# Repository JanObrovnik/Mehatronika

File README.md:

V tem repozitoriju so navedeni primeri kod v povezavi z našim izdelkom razvojne ploščice ESP32­-C3.

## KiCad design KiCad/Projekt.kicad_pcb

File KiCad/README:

Tukaj je celoten izdelek (vezje in ploščica) v KiCad-u..

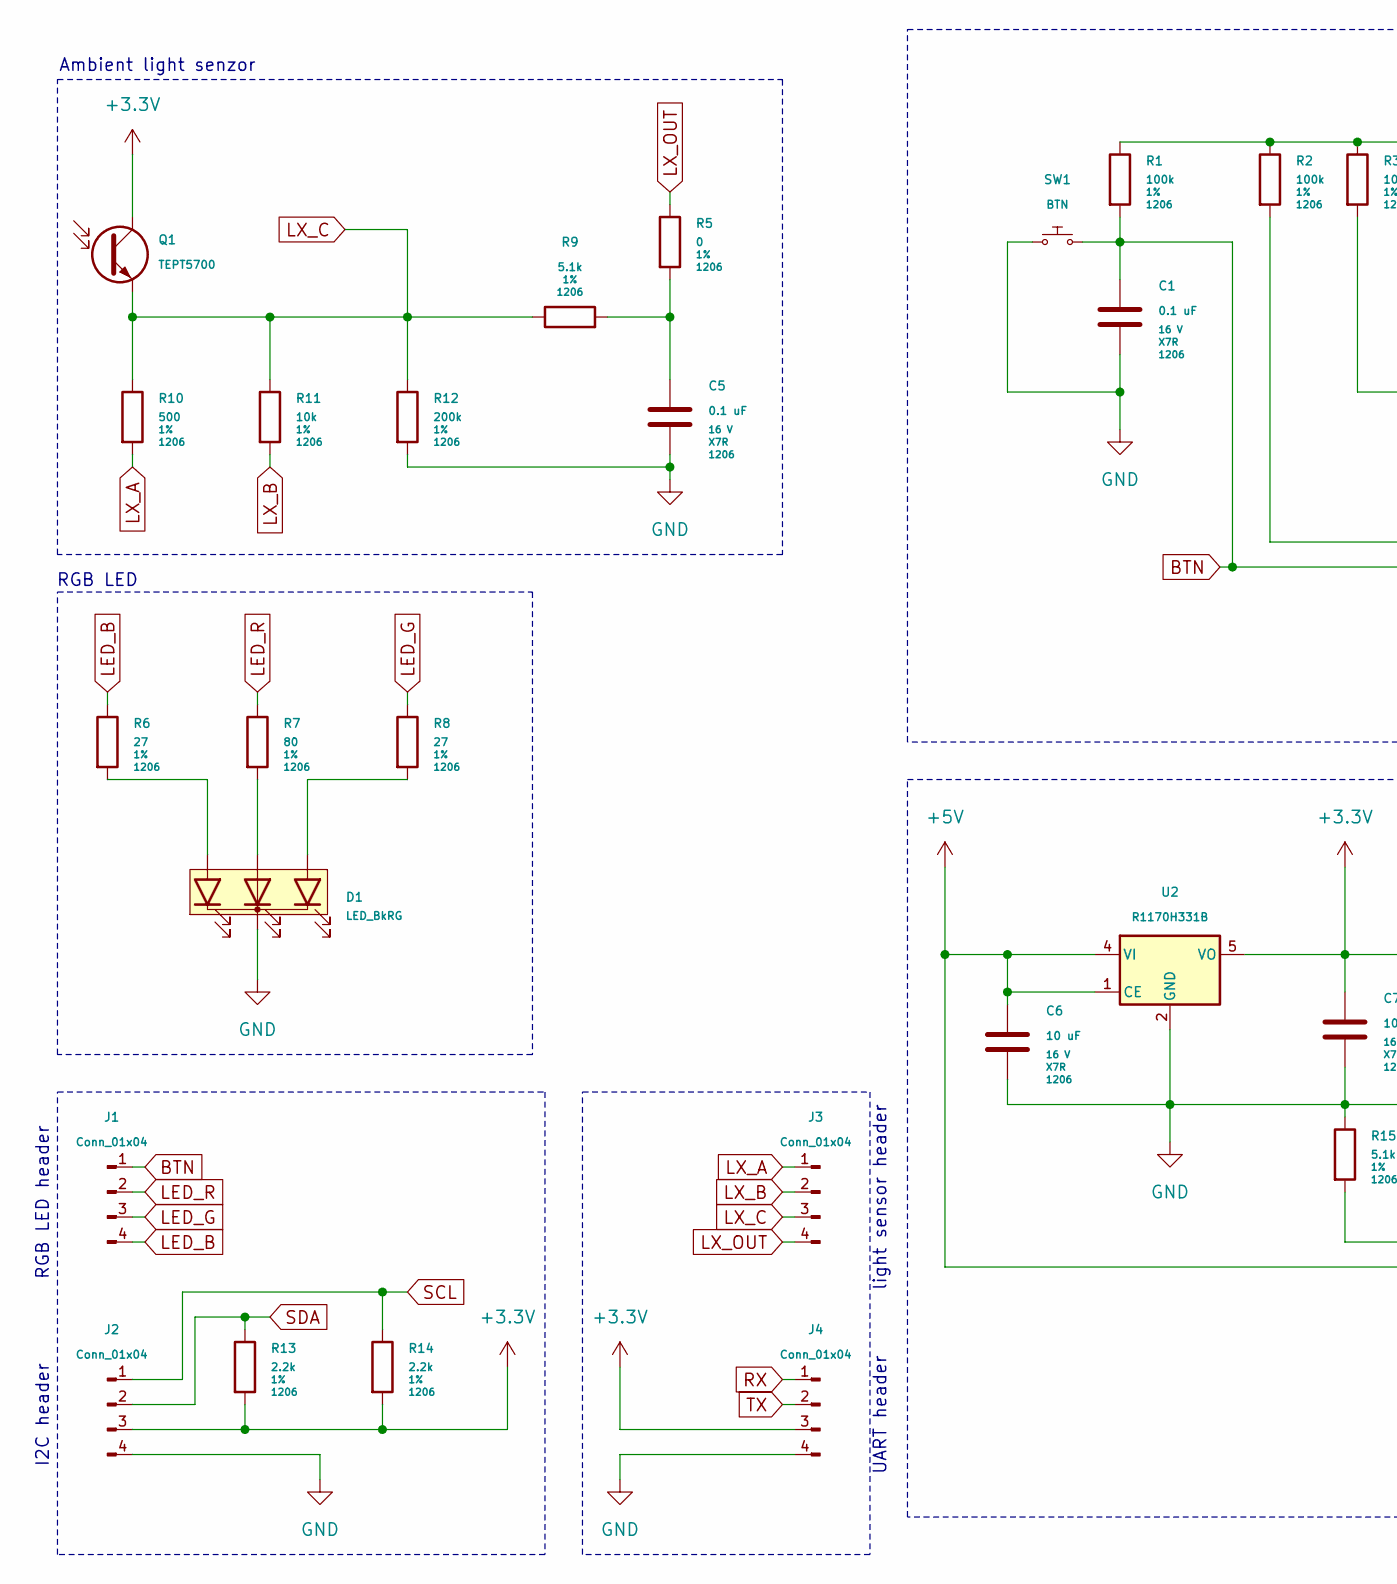
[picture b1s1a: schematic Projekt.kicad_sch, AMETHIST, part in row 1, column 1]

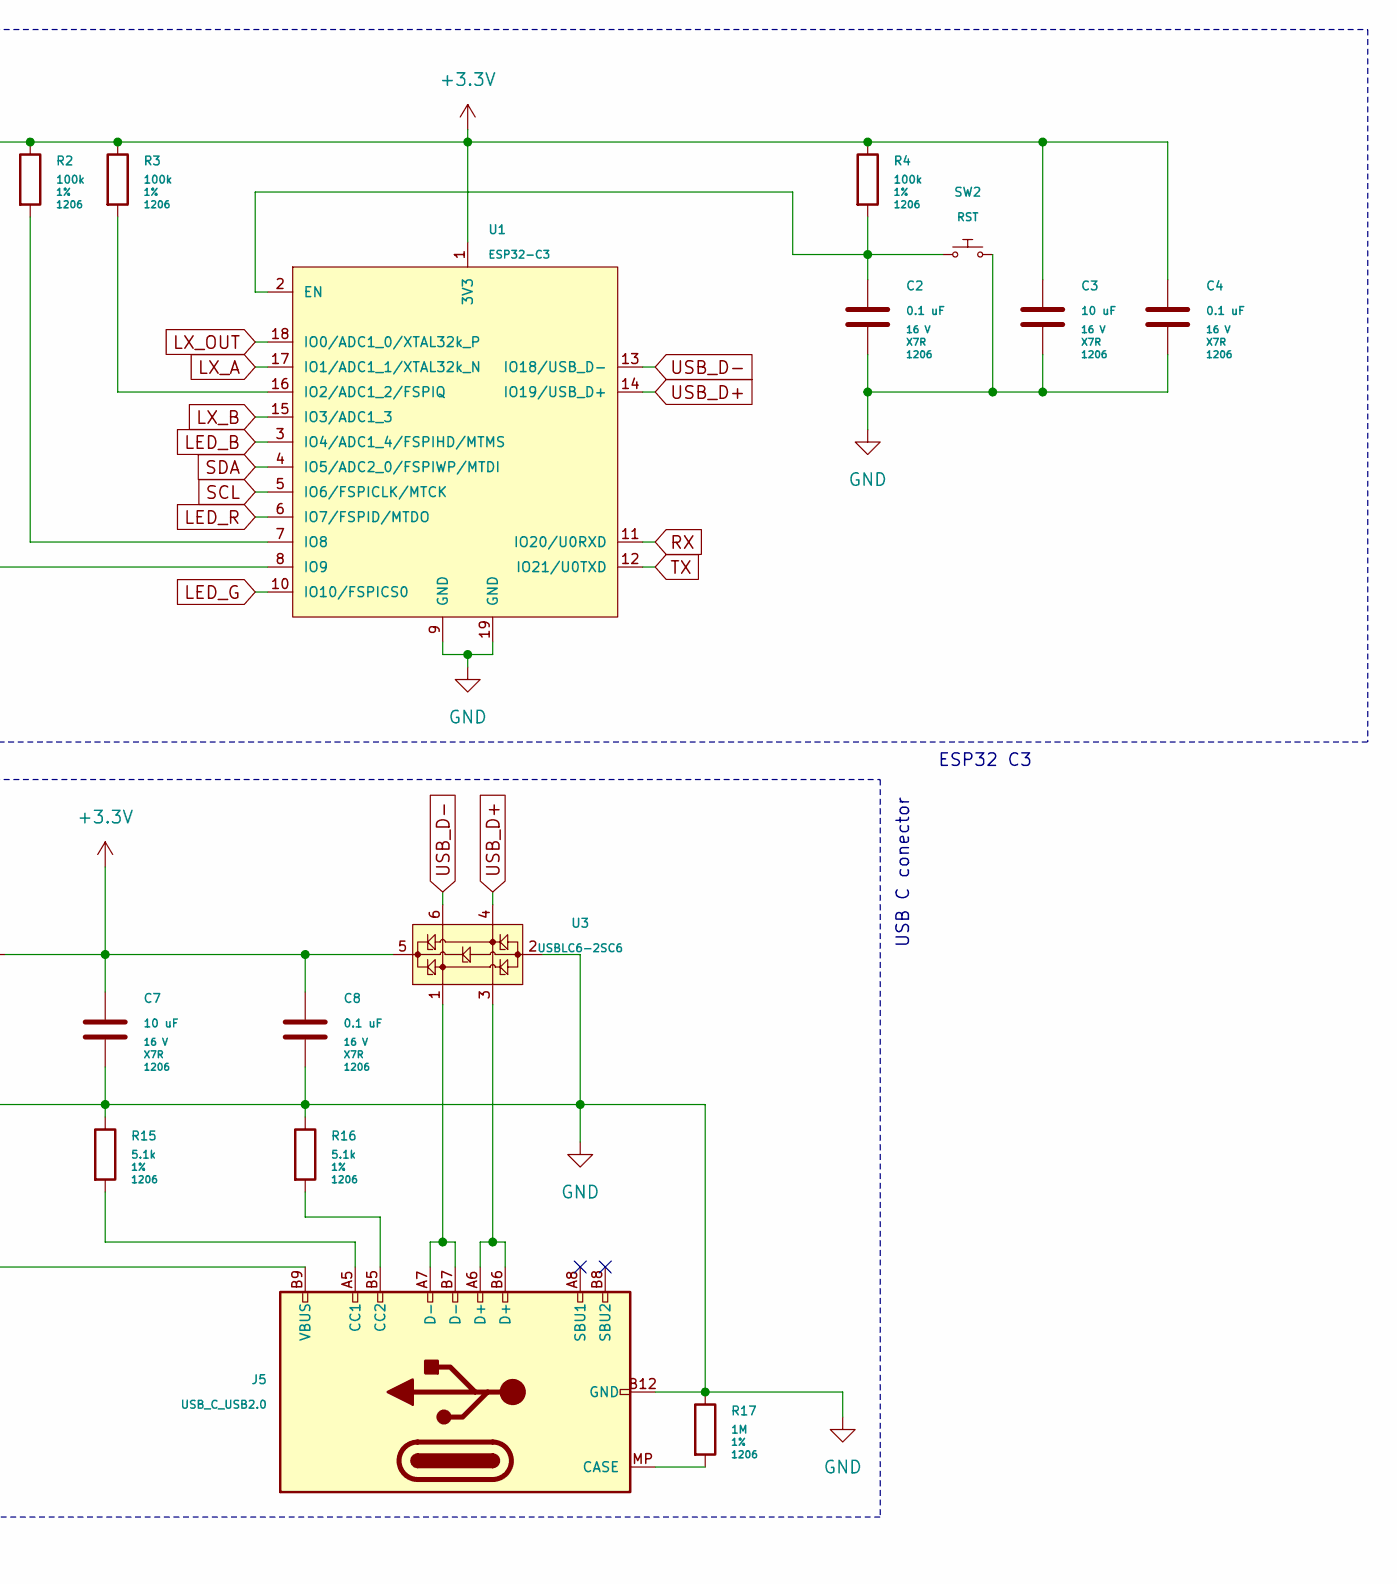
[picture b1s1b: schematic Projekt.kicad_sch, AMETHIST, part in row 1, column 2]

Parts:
C1, C2, C4, C5, C8: 0.1 uF; C_1206_(3216); Voltage 16 V; Tolerance X7R
C3, C6, C7: 10 uF; C_1206_(3216); Voltage 16 V; Tolerance X7R
D1: LED_BkRG; LED_D5.0mm-4_RGB
J1, J2, J3, J4: Conn_01x04; PinHeader_1x04_P2.54mm_Vertical
J5: USB_C_USB2.0; USB-C_MOLEX-216990-0001
Q1: TEPT5700; PT_D5.0mm
R1, R2, R3, R4: 100k; R_1206_(3216); Tolerance 1%
R5: 0; R_1206_(3216); Tolerance 1%
R6, R8: 27; R_1206_(3216); Tolerance 1%
R7: 80; R_1206_(3216); Tolerance 1%
R9, R15, R16: 5.1k; R_1206_(3216); Tolerance 1%
R10: 500; R_1206_(3216); Tolerance 1%
R11: 10k; R_1206_(3216); Tolerance 1%
R12: 200k; R_1206_(3216); Tolerance 1%
R13, R14: 2.2k; R_1206_(3216); Tolerance 1%
R17: 1M; R_1206_(3216); Tolerance 1%
SW1: BTN; SW_PUSH_6mm_SMD
SW2: RST; SW_PUSH_6mm_SMD
U1: ESP32-C3; ESP32-C3-WROOM-02
U2: R1170H331B; SOT-89-5
U3: USBLC6-2SC6; SOT-23-6

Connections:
+3.3V: C3.1, C4.1, C7.1, C8.1, J2.3, J4.3, Q1.C, R1.1, R2.1, R3.1, R4.1, R13.2, R14.2, U1.1 (3V3), U2.5 (VO), U3.5 (VBUS)
+5V: C6.1, J5.A4 (VBUS), J5.A9 (VBUS), J5.B4 (VBUS), J5.B9 (VBUS), U2.1 (CE), U2.4 (VI)
BTN: C1.1, J1.1, R1.2, SW1.COM, U1.8 (IO9); also elsewhere on the board
GND: C1.2, C2.2, C3.2, C4.2, C5.2, C6.2, C7.2, C8.2, D1.K, J2.4, J4.4, J5.A1 (GND), J5.A12 (GND), J5.B1 (GND), J5.B12 (GND), R12.2, R15.1, R16.1, R17.1, SW1.NO, SW2.COM, U1.9 (GND), U1.19 (GND), U2.2 (GND), U3.2 (GND); also elsewhere on the board
LED_B: J1.4, R6.1, U1.3 (IO4/ADC1_4/FSPIHD/MTMS)
LED_G: J1.3, R8.1, U1.10 (IO10/FSPICS0)
LED_R: J1.2, R7.1, U1.6 (IO7/FSPID/MTDO)
LX_A: J3.1, R10.2, U1.17 (IO1/ADC1_1/XTAL32k_N)
LX_B: J3.2, R11.2, U1.15 (IO3/ADC1_3)
LX_C: J3.3, Q1.E, R9.1, R10.1, R11.1, R12.1
LX_OUT: J3.4, R5.1, U1.18 (IO0/ADC1_0/XTAL32k_P)
unnamed: C5.1, R5.2, R9.2
unnamed: D1.Ab (Ablue), R6.2
unnamed: D1.Ag (Agreen), R8.2
unnamed: D1.Ar (Ared), R7.2
unnamed: J5.MP (CASE), R17.2
unnamed: J5.A5 (CC1), R15.2
unnamed: J5.B5 (CC2), R16.2
unnamed: J5.A6 (D+), J5.B6 (D+), U3.3 (I/O2)
unnamed: J5.A7 (D-), J5.B7 (D-), U3.1 (I/O1)
unnamed 20: C2.1, R4.2, SW2.NO, U1.2 (EN); also elsewhere on the board
unnamed: R3.2, U1.16 (IO2/ADC1_2/FSPIQ)
unnamed: R2.2, U1.7 (IO8)
RX: J4.1, U1.11 (IO20/U0RXD)
SCL: J2.1, R14.1, U1.5 (IO6/FSPICLK/MTCK)
SDA: J2.2, R13.1, U1.4 (IO5/ADC2_0/FSPIWP/MTDI)
TX: J4.2, U1.12 (IO21/U0TXD)
USB_D+: U1.14 (IO19/USB_D+), U3.4 (I/O2)
USB_D-: U1.13 (IO18/USB_D-), U3.6 (I/O1)

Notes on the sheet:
ESP32 C3
RGB LED header
UART header
I2C header
RGB LED
Ambient light senzor
light sensor header
USB C conector

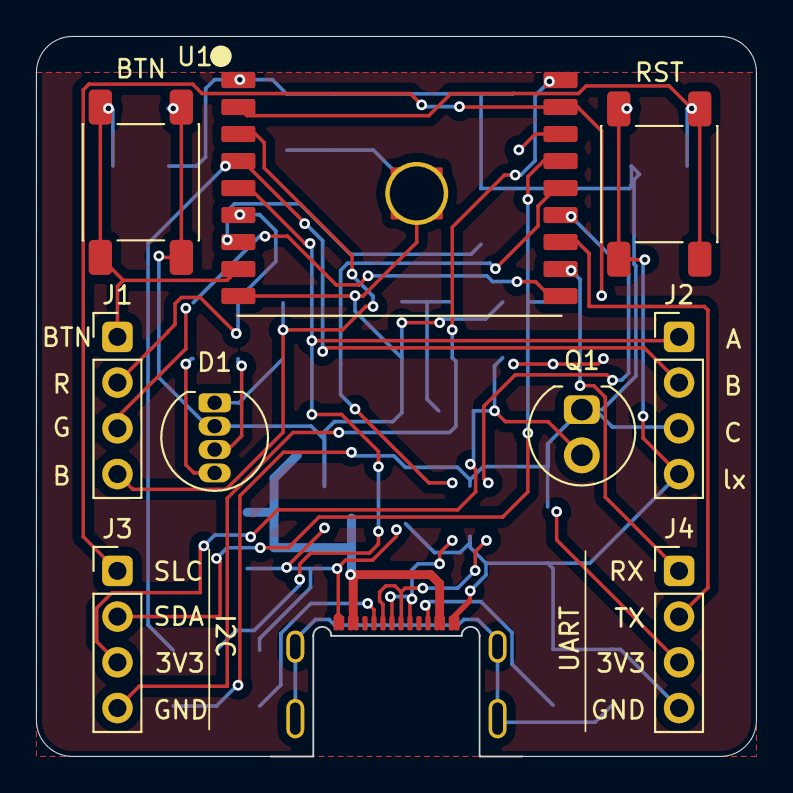
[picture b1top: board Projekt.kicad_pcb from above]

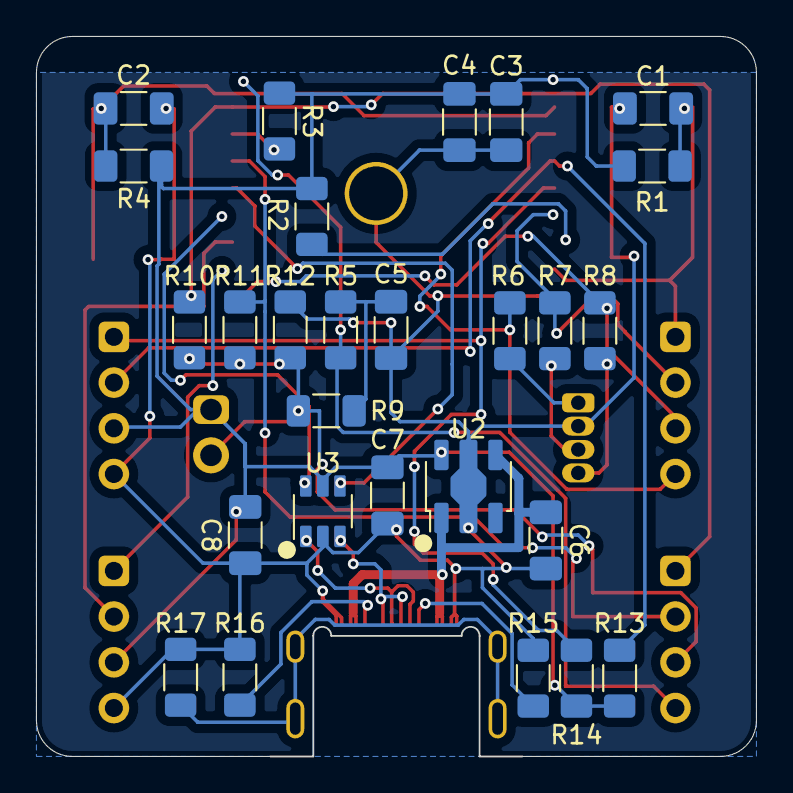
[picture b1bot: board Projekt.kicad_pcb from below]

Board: 2 copper layers, 40.0 x 40.0 mm, 37 parts (27 on the bottom side), 29 nets.

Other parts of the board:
BTN: BTN; SW_PUSH_6mm_SMD
RST: RST; SW_PUSH_6mm_SMD

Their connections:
BTN: BTN.COM; also elsewhere on the board
GND: BTN.NO, RST.COM; also elsewhere on the board
unnamed 20: RST.NO; also elsewhere on the board

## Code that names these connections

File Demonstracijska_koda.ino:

//-----Hardware-------------
//User button
#define BTN 9
//RGB LED
#define LED_R 7
#define LED_G 10
#define LED_B 4
//Ambient Light Sensor
#define LX_A 1
#define LX_B 3
#define LX_OUT 0
//I2C
#define SDA 5
#define SCL 6
//UART
#define RX 20
#define TX 21
//--------------------------

//-----Global variables-----
const int led_R_channel = 0;
const int led_G_channel = 1;
const int led_B_channel = 2;
const int pwm_frequency = 5000;//Hz
const int pwm_resolution = 12;//bit

//--------Variables---------
bool lock = false; // gumb spremeni v stikalo
bool hold = false; // preveri ali se gumb drzi ali ne
short time_hold = 0; // preveri koliko casa se gumb drzi
short time_release = 0; // preveri koliko casa je gumb sprescen
short count = 0; // steje klike (pravo stevilo je +1)
short brightness = 16; // svetlost lucke
short light = 0; // stopnja okoliske osvetljave
//--------------------------


//---------Gumb BTN---------
int btn(){
  return !digitalRead(BTN);
}

//-----------LED------------
void rgb(int R, int G, int B){
  ledcWrite(led_R_channel, R);
  ledcWrite(led_G_channel, G);
  ledcWrite(led_B_channel, B);
}

//-----Svetlobni senzor-----
int lx(int mode){
  switch(mode){
    case 0:
      pinMode(LX_A,INPUT);
      pinMode(LX_B,INPUT);
    break;
    case 1:
      pinMode(LX_A,INPUT);
      pinMode(LX_B,OUTPUT);
      digitalWrite(LX_B, LOW);
    break;
    case 2:
      pinMode(LX_A,OUTPUT);
      digitalWrite(LX_A, LOW);
      pinMode(LX_B,INPUT);
    break;
    default:
      pinMode(LX_A,INPUT);
      pinMode(LX_B,INPUT);
  }

  return analogRead(LX_OUT);
}


void setup() {
  pinMode(BTN,INPUT);

  pinMode(LED_R,OUTPUT);
  pinMode(LED_G,OUTPUT);
  pinMode(LED_B,OUTPUT);

  ledcSetup(led_R_channel, pwm_frequency, pwm_resolution);
  ledcAttachPin(LED_R, led_R_channel);
  ledcWrite(led_R_channel, 200);

  ledcSetup(led_G_channel, pwm_frequency, pwm_resolution);
  ledcAttachPin(LED_G, led_G_channel);
  ledcWrite(led_G_channel, 100);

  ledcSetup(led_B_channel, pwm_frequency, pwm_resolution);
  ledcAttachPin(LED_B, led_B_channel);
  ledcWrite(led_B_channel, 0);

  pinMode(LX_A,INPUT);
  pinMode(LX_B,INPUT);
  pinMode(LX_OUT,INPUT);

  Serial.begin(9600);
  delay(1000);
  Serial.println("Erasmus+\nGEMS\nAmethyst\nv0.0\n\n");
}

void loop() {
  delay(100);

  if(btn()){

    if(time_hold == 0 && time_release <= 6) {
      count++;
    }

    time_hold++;
    time_release = 0;

    if(time_hold > 68) {brightness = 0; rgb(brightness,brightness,brightness);}
    else if(time_hold > 60) {brightness = 6; rgb(brightness,brightness,brightness);}
    else if(time_hold > 52) {brightness = 16; rgb(brightness,brightness,brightness);}
    else if(time_hold > 44) {brightness = 51; rgb(brightness,brightness,brightness);}
    else if(time_hold > 36) {brightness = 102; rgb(brightness,brightness,brightness);}
    else if(time_hold > 28) {brightness = 153; rgb(brightness,brightness,brightness);}
    else if(time_hold > 20) {brightness = 204; rgb(brightness,brightness,brightness);}
    else if(time_hold > 12) {brightness = 255; rgb(brightness,brightness,brightness); count = 0;}

    if(hold == false) {

      if(lock == true) {
        lock = false;
      }
      else if(lock == false) {
        rgb(0,0,brightness);
        lock = true;
      }
      hold = true;
    }
  }

  else {
    hold = false;
    time_hold = 0;
    time_release++;

    if(time_release > 100) time_release = 20;
    else if(time_release > 6) {
      if (count == 2) {light = 0; rgb(16,0,8); delay(2000);}
      else if (count == 3) {light = 1; rgb(120,0,60); delay(2000);}
      else if (count == 4) {light = 2; rgb(250,0,125); delay(2000);}
      count = 0;
    }

    if(lock == true) {
      rgb(0,0,brightness);
    }
    else if(lx(light) < (800/(light+1))){
      rgb(brightness,0,0);
    }
    else{
      rgb(0,brightness,0);
    }
  }
}

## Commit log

2024-05-12 Naložitev primera uporabe UART
2024-05-14 Naložitev demonstracijskega programa
2024-05-14 KiCad projekt
2024-05-20 Popravek sheme board
2024-07-16 Implementacija programa
